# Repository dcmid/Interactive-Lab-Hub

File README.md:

[BugBot](https://github.com/dcmid/BugBot)

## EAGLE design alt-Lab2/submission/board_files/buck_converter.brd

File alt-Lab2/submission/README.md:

# Alt Lab 2
## Part A. Design your Arduino+

**a) What is the + improvement of your Arduino+**  
I have implemented a buck converter -- a simple, pwm-controlled DC step-down converter -- which allows the analogOut() function to be used to output actual analog voltages.

**b) What Arduino form-factor/design are you basing your design off of?**  
I have implemented my design as a daughter card that can hooked up to any pwm, so it is compatible with any Arduino form factor.

**c) What features/parts need to be incorporated for your Arduino+? Include your research!**  
The buck converter is basically a charge pump and lowpass filter. It is constructed entirely of basic circuit components (transistor, capacitor, inductor, diode)

**d) What is the timeline for the overall development of your Arduino?**  
The PCB has been ordered and should arrive within a couple of weeks.

**e) Which fabrication company are you using, what do you plan to order, and what is the design rationale for the selection?**  
I am using OSH Park. I ordered a set of PCBs from them. I did not order components or assembly, as I already have the components here and the assembly will be simple.

## Part B. Order parts for your Arduino+

I already own enough generic electronics components to complete this board. I have listed the models that I will be using, selected largely based on what I have on-hand, in the table below.

| Part     | Model | Quantity |
|----------|-------|----------|
|MOSFET    |BS170  |1         |
|Diode     |1N4007 |1         |
|Inductor  |Generic|1         |
|Resistor  |Generic|1         |
|Pin Header|Generic|5         |

## Part C. Prototype your Arduino+

**Describe key design questions (how big are the parts? what pins need to be connected?) and how you used/will use prototyping to answer them.**  
The values for the capacitor, inductor, and resistor must be selected. This can be achieved through simulation and experimentation on a breadboard.

## Part D. Layout your Arduino+

**Document what you files, with enough specificity that anyone else could have the same thing made.**  
I have created design files with Eagle. The preview image of the board is shown here.  

## Part E. Send your board off to be made
**Document what you sent, and to where, with enough specificity that anyone else could have the same thing made.**  
I ordered the board (design files included in this repo) from OSH Park.

**In the report, please tell us any pain points you faced in this lab, and how we could make this process easier for future students.**  
I believe that having students design a separate board like I did, rather than modify an existing Arduino design, would be a much more approachable and helpful introduction to PCB design.

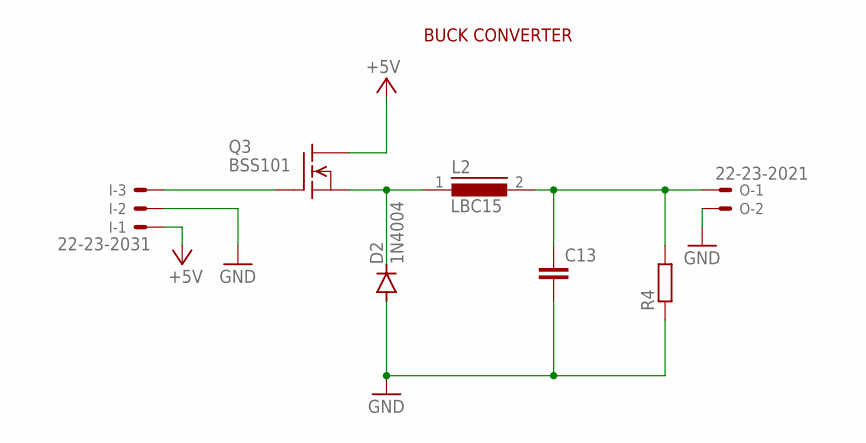
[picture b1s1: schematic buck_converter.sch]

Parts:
C13: C2.5/2; C2.5-2
D2: 1N4004; DO41-10
I: 22-23-2031
L2: LBC15
O: 22-23-2021
Q3: BSS101; TO92
R4: R-EU_0207/10; 0207/10

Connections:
+5V: I.1, Q3.3 (D)
BCO: C13.1, L2.2, O.1, R4.2
GND: C13.2, D2.A, I.2, O.2, R4.1
unnamed: I.3, Q3.2 (G)
unnamed: D2.C, L2.1, Q3.1 (S)

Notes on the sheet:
BUCK CONVERTER

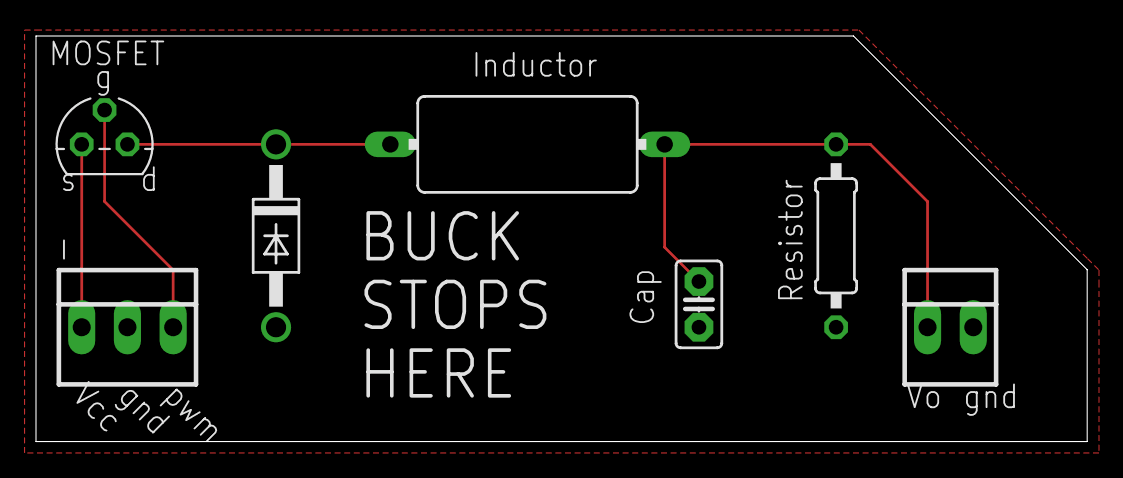
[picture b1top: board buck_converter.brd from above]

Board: 2 copper layers, 58.4 x 22.5 mm, 7 parts (0 on the bottom side), 5 nets.

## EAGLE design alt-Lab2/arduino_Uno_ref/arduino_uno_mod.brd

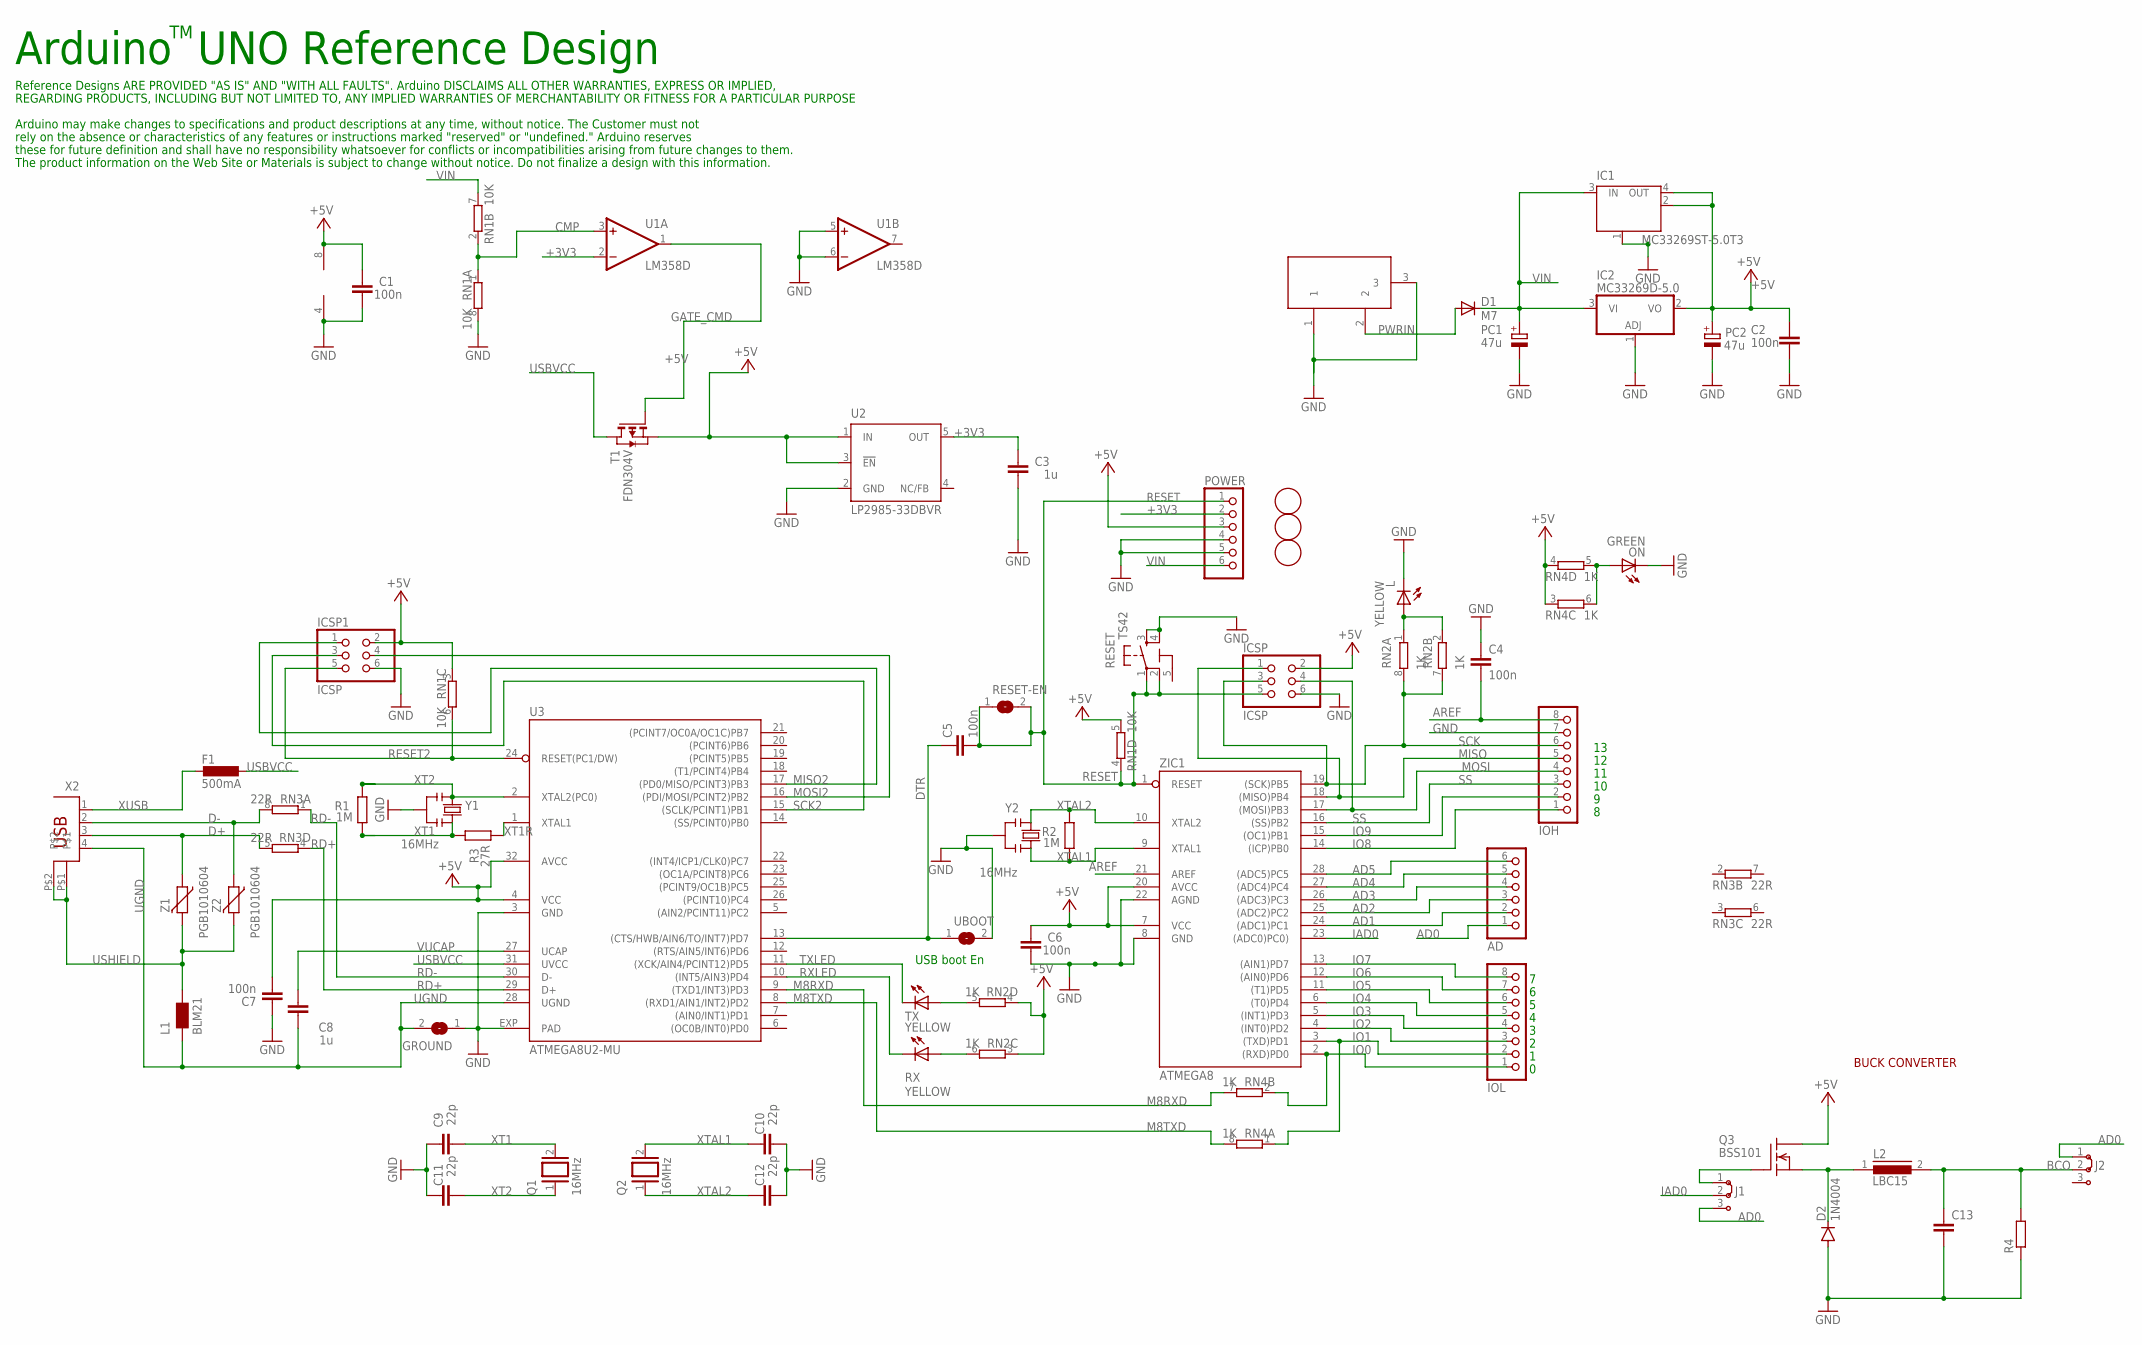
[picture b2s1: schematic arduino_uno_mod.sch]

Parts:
AD: PINHD-1X6; 1X06
C1, C2, C4, C5, C6, C7: 100n; C0603-ROUND
C3, C8: 1u; C0603-ROUND
C9, C10, C11, C12: 22p; C0603-ROUND
C13: C2.5/2; C2.5-2
D1: M7; SMB
D2: 1N4004; DO41-10
F1: 500mA; L1812
GROUND: SJ
IC1: MC33269ST-5.0T3; SOT223
IC2: MC33269D-5.0; DPACK
ICSP, ICSP1: ICSP; 2X03
IOH: PINHD-1X8; 1X08
IOL: PINHD-1X8; 1X08
J1, J2: J2X2MM; 04C
L: YELLOW; CHIP-LED0805
L1: BLM21; 0805
L2: LBC15
ON: GREEN; CHIP-LED0805
PC1, PC2: 47u; PANASONIC_D
POWER: PINHD-1X6; 1X06
Q1, Q2: 16MHz; QS
Q3: BSS101; TO92
R1, R2: 1M; R0603-ROUND
R3: 27R; R0603-ROUND
R4: R-EU_0207/10; 0207/10
RESET: TS42
RESET-EN: SJ
RN1: 10K; CAY16
RN2, RN4: 1K; CAY16
RN3: 22R; CAY16
RX: YELLOW; CHIP-LED0805
T1: FDN304V; SOT-23
TX: YELLOW; CHIP-LED0805
U1: LM358D; SO08
U2: LP2985-33DBVR; SOT23-DBV
U3: ATMEGA8U2-MU; QFN32
U$3, U$4, U$6: FIDUCIALMOUNT; FIDUCIA-MOUNT
UBOOT: SJ
X1: DC21MMX; DC-21MM
X2: PN61729
Y1, Y2: 16MHz; RESONATOR
Z1, Z2: PGB1010604; CT/CN0603
ZIC1: ATMEGA8; DIL28-3

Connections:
5-GND: RESET.5 (5-GND)
+3V3: C3.2, POWER.2, U1.2 (-IN), U2.5 (OUT)
+5V: C1.2, C2.2, C6.2, C7.1, IC1.2 (OUT), IC1.4 (OUT), IC2.2 (VO), ICSP.2, ICSP1.2, PC2.+, POWER.3, Q3.3 (D), RN1.3 (1), RN1.5 (2), RN2.3 (1), RN2.4 (1), RN4.3 (1), RN4.4 (1), T1.2 (S), U1.8 (V+), U2.1 (IN), U2.3 (!EN), U3.4 (VCC), U3.32 (AVCC), ZIC1.7 (VCC), ZIC1.20 (AVCC)
AD0: AD.1, J1.3, J2.1
AD1: AD.2, ZIC1.24 ((ADC1)PC1)
AD2: AD.3, ZIC1.25 ((ADC2)PC2)
AD3: AD.4, ZIC1.26 ((ADC3)PC3)
AD4: AD.5, ZIC1.27 ((ADC4)PC4)
AD5: AD.6, ZIC1.28 ((ADC5)PC5)
AREF: C4.2, IOH.8, ZIC1.21 (AREF)
BCO: C13.1, J2.2, L2.2, R4.2
CMP: RN1.1, RN1.2 (1), U1.3 (+IN)
D+: RN3.5 (2), X2.3, Z1.1
D-: RN3.8 (2), X2.2, Z2.1
DTR: C5.1, U3.13 ((CTS/HWB/AIN6/TO/INT7)PD7), UBOOT.1
GATE_CMD: T1.3 (G), U1.1 (OUT)
GND: C1.1, C2.1, C3.1, C4.1, C6.1, C7.2, C9.2, C10.1, C11.2, C12.1, C13.2, D2.A, GROUND.1, IC1.1 (GND/ADJ), IC2.1 (ADJ), ICSP.6, ICSP1.6, IOH.7, L.C, ON.C, PC1.-, PC2.-, POWER.4, POWER.5, R4.1, RESET.3, RESET.4, RN1.8 (2), U1.4 (V-), U1.5 (+IN), U1.6 (-IN), U2.2 (GND), U3.3 (GND), U3.EXP (PAD), UBOOT.2, X1.1, X1.3, Y1.2, Y2.2, ZIC1.8 (GND), ZIC1.22 (AGND)
IAD0: J1.2, ZIC1.23 ((ADC0)PC0))
IO0: IOL.1, RN4.2 (1), ZIC1.2 ((RXD)PD0)
IO1: IOL.2, RN4.1, ZIC1.3 ((TXD)PD1)
IO2: IOL.3, ZIC1.4 ((INT0)PD2)
IO3: IOL.4, ZIC1.5 ((INT1)PD3)
IO4: IOL.5, ZIC1.6 ((T0)PD4)
IO5: IOL.6, ZIC1.11 ((T1)PD5)
IO6: IOL.7, ZIC1.12 ((AIN0)PD6)
IO7: IOL.8, ZIC1.13 ((AIN1)PD7)
IO8: IOH.1, ZIC1.14 ((ICP)PB0)
IO9: IOH.2, ZIC1.15 ((OC1)PB1)
M8RXD: RN4.7 (2), U3.9 ((TXD1/INT3)PD3)
M8TXD: RN4.8 (2), U3.8 ((RXD1/AIN1/INT2)PD2)
MISO: ICSP.1, IOH.5, ZIC1.18 ((MISO)PB4)
MISO2: ICSP1.1, U3.17 ((PD0/MISO/PCINT3)PB3)
MOSI: ICSP.4, IOH.4, ZIC1.17 ((MOSI)PB3)
MOSI2: ICSP1.4, U3.16 ((PDI/MOSI/PCINT2)PB2)
unnamed: J1.1, Q3.2 (G)
unnamed: L.A, RN2.1, RN2.2 (1)
unnamed: ON.A, RN4.5 (2), RN4.6 (2)
unnamed: D2.C, L2.1, Q3.1 (S)
unnamed: RN2.6 (2), RX.A
unnamed: RN2.5 (2), TX.A
PWRIN: D1.A, X1.2
RD+: RN3.4 (1), U3.29 (D+)
RD-: RN3.1, U3.30 (D-)
RESET: C5.2, ICSP.5, POWER.1, RESET.1, RESET.2, RESET-EN.1, RESET-EN.2, RN1.4 (1), ZIC1.1 (RESET)
RESET2: ICSP1.5, RN1.6 (2), U3.24 (RESET(PC1/DW))
RXLED: RX.C, U3.10 ((INT5/AIN3)PD4)
SCK: ICSP.3, IOH.6, RN2.7 (2), RN2.8 (2), ZIC1.19 ((SCK)PB5)
SCK2: ICSP1.3, U3.15 ((SCLK/PCINT1)PB1)
SS: IOH.3, ZIC1.16 ((SS)PB2)
TXLED: TX.C, U3.11 ((XCK/AIN4/PCINT12)PD5)
UGND: C8.2, GROUND.2, L1.1, U3.28 (UGND), X2.4
USBVCC: F1.1, T1.1 (D), U3.31 (UVCC)
USHIELD: L1.2, X2.P$1, X2.P$2, Z1.2, Z2.2
VIN: D1.C, IC1.3 (IN), IC2.3 (VI), PC1.+, POWER.6, RN1.7 (2)
VUCAP: C8.1, U3.27 (UCAP)
XT1: C9.1, Q1.2, R1.1, R3.2, Y1.3
XT1R: R3.1, U3.1 (XTAL1)
XT2: C11.1, Q1.1, R1.2, U3.2 (XTAL2(PC0)), Y1.1
XTAL1: C10.2, Q2.2, R2.1, Y2.3, ZIC1.9 (XTAL1)
XTAL2: C12.2, Q2.1, R2.2, Y2.1, ZIC1.10 (XTAL2)
XUSB: F1.2, X2.1

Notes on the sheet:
Arduino UNO Reference Design
USB boot En
Reference Designs ARE PROVIDED "AS IS" AND "WITH ALL FAULTS". Arduino DISCLAIMS ALL OTHER WARRANTIES, EXPRESS OR IMPLIED,
Arduino may make changes to specifications and product descriptions at any time, without notice. The Customer must not
REGARDING PRODUCTS, INCLUDING BUT NOT LIMITED TO, ANY IMPLIED WARRANTIES OF MERCHANTABILITY OR FITNESS FOR A PARTICULAR PURPOSE
rely on the absence or characteristics of any features or instructions marked "reserved" or "undefined." Arduino reserves
these for future definition and shall have no responsibility whatsoever for conflicts or incompatibilities arising from future changes to them.
The product information on the Web Site or Materials is subject to change without notice. Do not finalize a design with this information.
BUCK CONVERTER

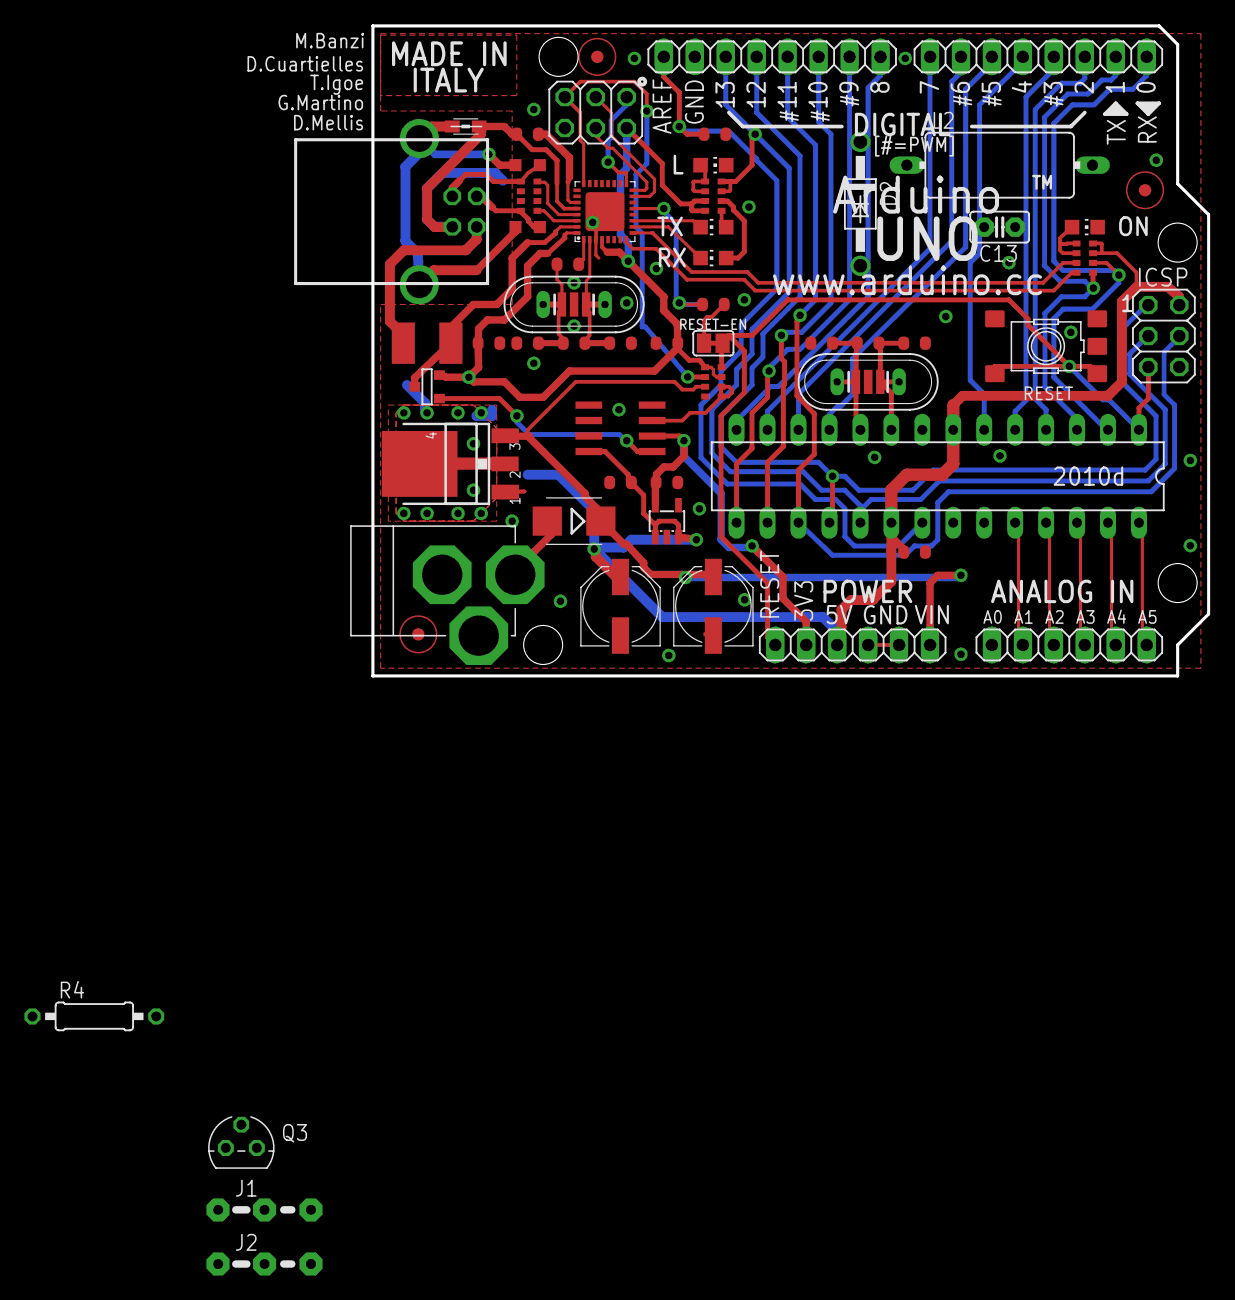
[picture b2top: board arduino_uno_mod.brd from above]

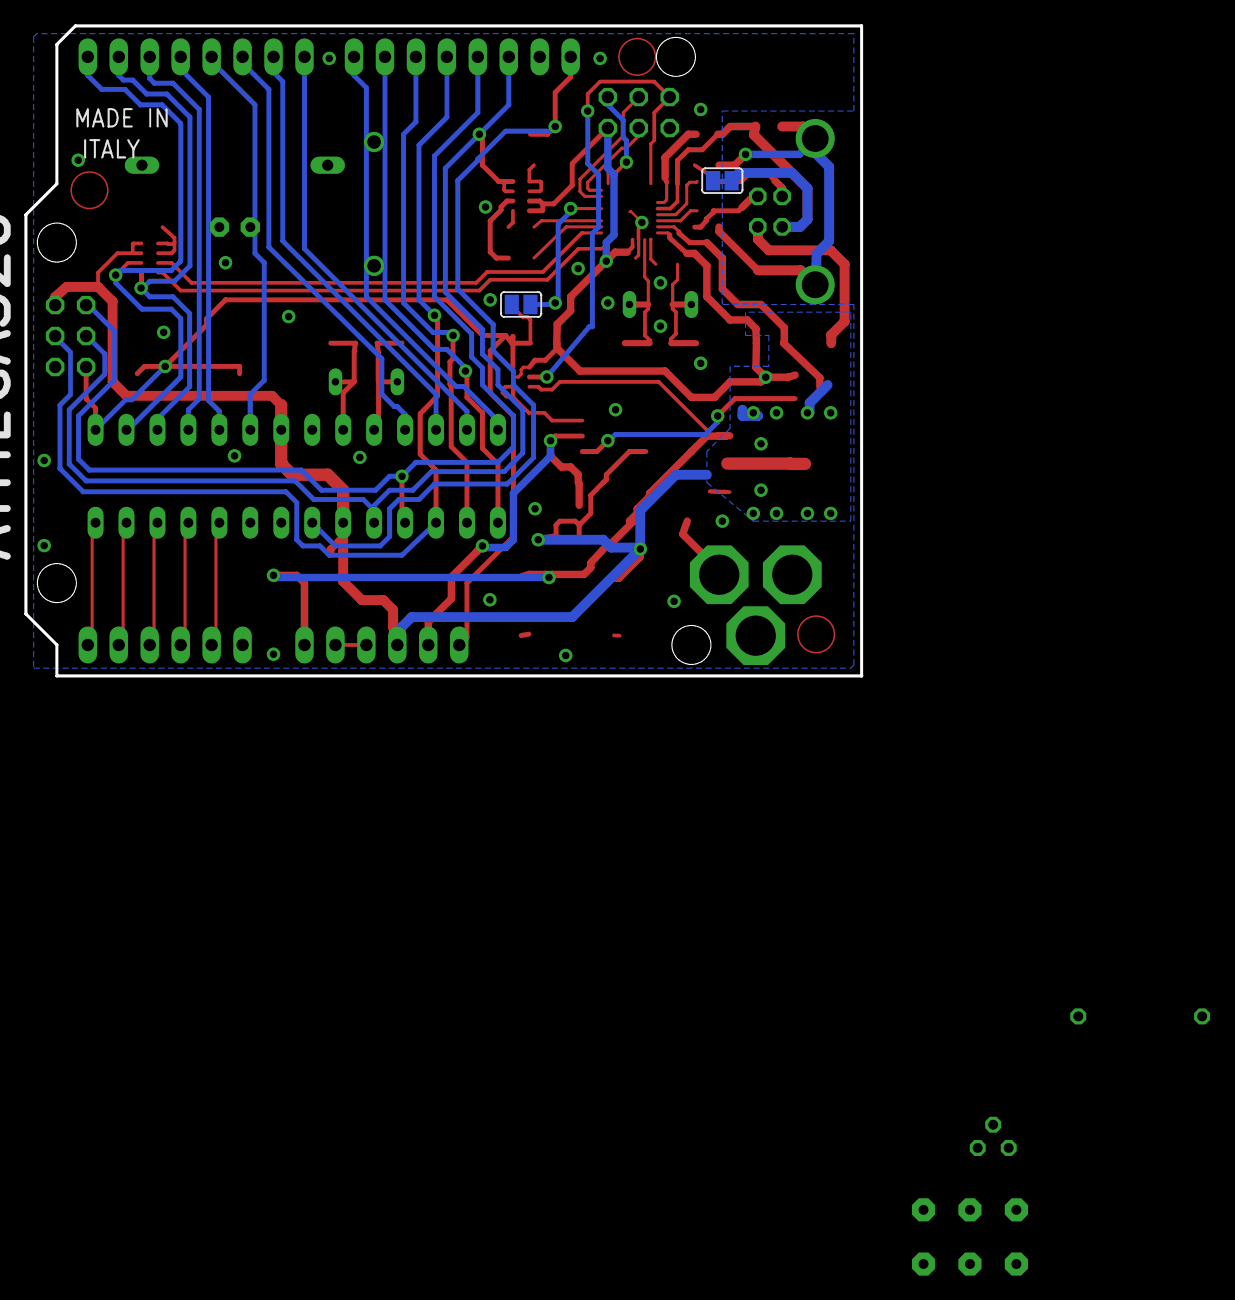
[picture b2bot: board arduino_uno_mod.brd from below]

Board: 2 copper layers, 68.6 x 53.3 mm, 63 parts (2 on the bottom side), 60 nets.

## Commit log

2020-09-10 added Lab1
2020-09-11 added prelab for alt lab 2
2020-09-11 made correction to prelab 2 readme
2020-09-12 moved alt lab 1 submission to correct directory
2020-09-15 added board design
2020-09-17 pre-merge commit
2020-09-17 added design files for buck converter
2020-09-17 added readme for alt lab 2
2020-09-22 added completed Lab3
2020-09-22 added missing video
2020-10-08 working on alt lab 5
2020-10-14 Lab4 mostly done
2020-10-14 added media, updated readme
2020-10-14 Lab4 complete
2020-10-15 Alt Lab5 complete
2020-10-22 working on Lab6
2020-10-26 Lab6 progress
2020-10-26 finished custom chatbot
2020-10-26 finished Lab6 readme
2020-10-26 saved README
2020-10-27 Lab7 progress
2020-10-27 Thru simple MQTT
2020-10-28 finished Lab7
2020-11-12 Added Final Project Link
